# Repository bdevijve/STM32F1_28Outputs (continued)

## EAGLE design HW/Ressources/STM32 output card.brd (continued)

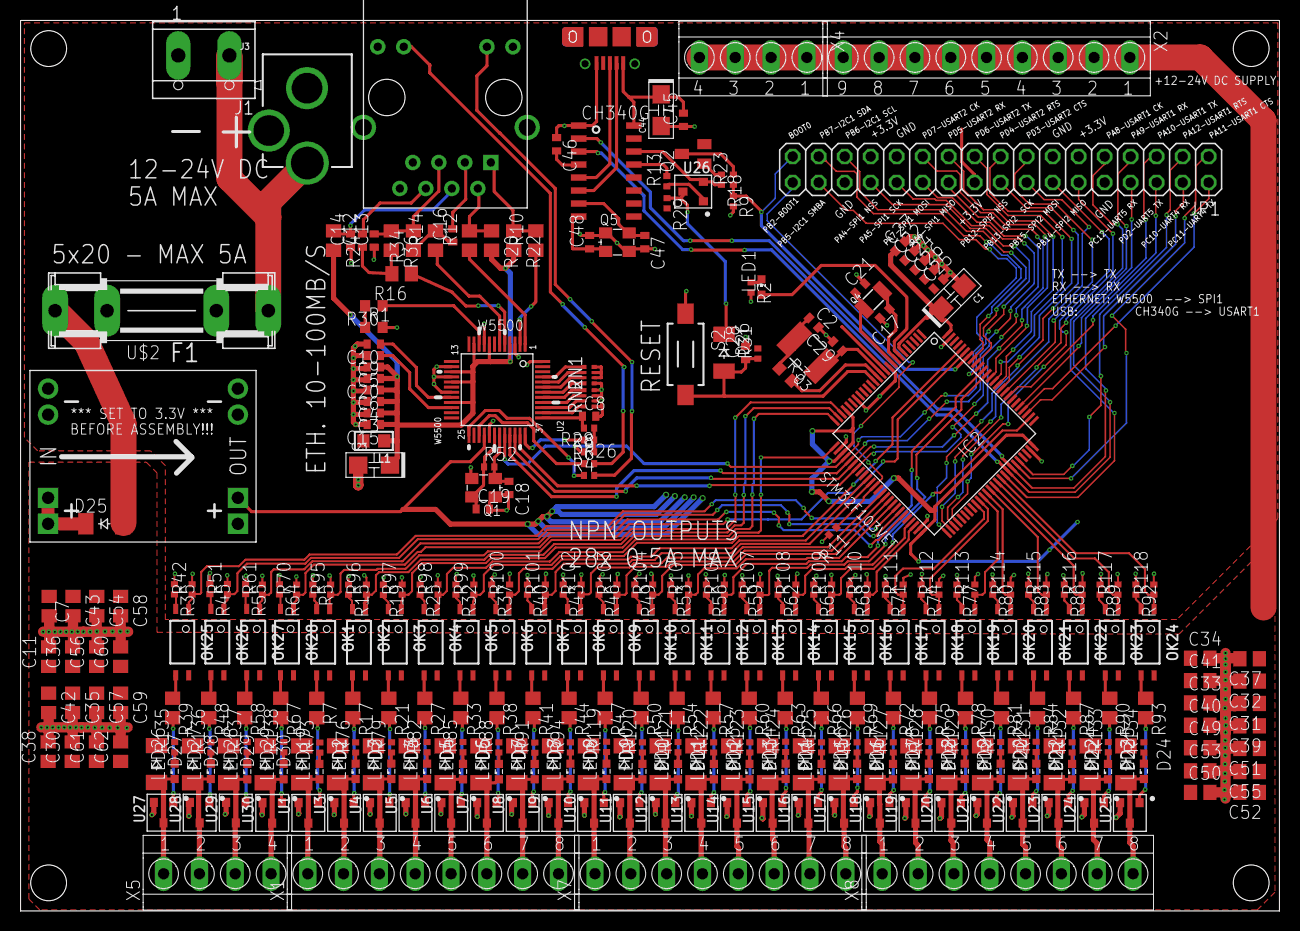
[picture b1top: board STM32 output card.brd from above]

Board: 2 copper layers, 123.0 x 87.0 mm, 341 parts (0 on the bottom side), 253 nets.

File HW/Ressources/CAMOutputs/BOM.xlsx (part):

COMMENT | DESIGNATOR | FOOTPRINT | Device | Description | PART NUMBER
 | LED1 | CHIP-LED0603 |  | LED | C2286
 | LED2 | SML0603 |  | LED | C2286
 | LED3 | SML0603 |  | LED | C2286
 | LED4 | SML0603 |  | LED | C2286
 | LED5 | SML0603 |  | LED | C2286
 | LED6 | SML0603 |  | LED | C2286
 | LED7 | SML0603 |  | LED | C2286
 | LED8 | SML0603 |  | LED | C2286
 | LED9 | SML0603 |  | LED | C2286
 | LED10 | SML0603 |  | LED | C2286
 | LED11 | SML0603 |  | LED | C2286
 | LED12 | SML0603 |  | LED | C2286
 | LED13 | SML0603 |  | LED | C2286
 | LED14 | SML0603 |  | LED | C2286
 | LED15 | SML0603 |  | LED | C2286
 | LED16 | SML0603 |  | LED | C2286
 | LED17 | SML0603 |  | LED | C2286
 | LED18 | SML0603 |  | LED | C2286
 | LED19 | SML0603 |  | LED | C2286
 | LED20 | SML0603 |  | LED | C2286
 | LED21 | SML0603 |  | LED | C2286
 | LED22 | SML0603 |  | LED | C2286
 | LED23 | SML0603 |  | LED | C2286
 | LED24 | SML0603 |  | LED | C2286
 | LED25 | SML0603 |  | LED | C2286
 | LED26 | SML0603 |  | LED | C2286
 | LED27 | SML0603 |  | LED | C2286
 | LED28 | SML0603 |  | LED | C2286
 | LED29 | SML0603 |  | LED | C2286
100K | R9 | R0402 |  | RESISTOR, European symbol | C25741
100K | R11 | R0402 |  | RESISTOR, European symbol | C25741
100K | R42 | R0402 |  | RESISTOR, European symbol | C25741
100K | R51 | R0402 |  | RESISTOR, European symbol | C25741
100K | R61 | R0402 |  | RESISTOR, European symbol | C25741
100K | R70 | R0402 |  | RESISTOR, European symbol | C25741
100K | R95 | R0402 |  | RESISTOR, European symbol | C25741
100K | R96 | R0402 |  | RESISTOR, European symbol | C25741
100K | R97 | R0402 |  | RESISTOR, European symbol | C25741
100K | R98 | R0402 |  | RESISTOR, European symbol | C25741
100K | R99 | R0402 |  | RESISTOR, European symbol | C25741
100K | R100 | R0402 |  | RESISTOR, European symbol | C25741
100K | R101 | R0402 |  | RESISTOR, European symbol | C25741
100K | R102 | R0402 |  | RESISTOR, European symbol | C25741
100K | R103 | R0402 |  | RESISTOR, European symbol | C25741
100K | R104 | R0402 |  | RESISTOR, European symbol | C25741
100K | R105 | R0402 |  | RESISTOR, European symbol | C25741
100K | R106 | R0402 |  | RESISTOR, European symbol | C25741
100K | R107 | R0402 |  | RESISTOR, European symbol | C25741
100K | R108 | R0402 |  | RESISTOR, European symbol | C25741
100K | R109 | R0402 |  | RESISTOR, European symbol | C25741
100K | R110 | R0402 |  | RESISTOR, European symbol | C25741
100K | R111 | R0402 |  | RESISTOR, European symbol | C25741
100K | R112 | R0402 |  | RESISTOR, European symbol | C25741
100K | R113 | R0402 |  | RESISTOR, European symbol | C25741
100K | R114 | R0402 |  | RESISTOR, European symbol | C25741
100K | R115 | R0402 |  | RESISTOR, European symbol | C25741
100K | R116 | R0402 |  | RESISTOR, European symbol | C25741
100K | R117 | R0402 |  | RESISTOR, European symbol | C25741
100K | R118 | R0402 |  | RESISTOR, European symbol | C25741
100nF | C3 | C0402 |  | CAPACITOR, European symbol | C1525
100nF | C4 | C0402 |  | CAPACITOR, European symbol | C1525
100nF | C5 | C0402 |  | CAPACITOR, European symbol | C1525
100nF | C6 | C0402 |  | CAPACITOR, European symbol | C1525
100nF | C8 | C0402 |  | CAPACITOR, European symbol | C1525
100nF | C15 | C0402 |  | CAPACITOR, European symbol | C1525
100nF | C20 | C0402 |  | CAPACITOR, European symbol | C1525
100nF | C22 | C0402 |  | CAPACITOR, European symbol | C1525
100nF | C24 | C0402 |  | CAPACITOR, European symbol | C1525
100nF | C25 | C0402 |  | CAPACITOR, European symbol | C1525
100nF | C26 | C0402 |  | CAPACITOR, European symbol | C1525
100nF | C27 | C0402 |  | CAPACITOR, European symbol | C1525
100pF | C45 | C0402 |  | CAPACITOR, European symbol | C1546
100pF | C46 | C0402 |  | CAPACITOR, European symbol | C1546
10K | R4 | R0402 |  | RESISTOR, European symbol | C25744
10K | R6 | R0402 |  | RESISTOR, European symbol | C25744
10K | R8 | R0402 |  | RESISTOR, European symbol | C25744
10K | R29 | R0402 |  | RESISTOR, European symbol | C25744
10K | R31 | R0402 |  | RESISTOR, European symbol | C25744
10K | RN1 | 4X0402ARV341 |  | Array Chip Resistor | C25725
10K | RN2 | 4X0402ARV341 |  | Array Chip Resistor | C25725
10nF | C9 | C0402 |  | CAPACITOR, European symbol | C15195
10nF | C13 | C0402 |  | CAPACITOR, European symbol | C15195
10pF | C17 | C0402 |  | CAPACITOR, European symbol | C32949
10pF | C21 | C0402 |  | CAPACITOR, European symbol | C32949
10uF/16V | C1 | C-3216(TANTAL) |  |  | C7171
10uF/16V | C23 | C-3216(TANTAL) |  |  | C7171
10uF/16V | C44 | C-3216(TANTAL) |  |  | C7171
12MHz | Q5 | 3.2X2.5_KX-7 |  | Quartz Crystals (MHz) SMD: | C9002
18pF | C18 | C0402 |  | CAPACITOR, European symbol | C1549
18pF | C19 | C0402 |  | CAPACITOR, European symbol | C1549
1ÂµF | C28 | C0402 |  | CAPACITOR, European symbol | C52923
1K | R13 | R0402 |  | RESISTOR, European symbol | C11702
1K | R18 | R0402 |  | RESISTOR, European symbol | C11702
1K | R23 | R0402 |  | RESISTOR, European symbol | C11702
1M | R52 | R0402 |  | RESISTOR, European symbol | C26083
20pF | C2 | C0402 |  | CAPACITOR, European symbol | C1554
20pF | C29 | C0402 |  | CAPACITOR, European symbol | C1554
22nF | C14 | C0402 |  | CAPACITOR, European symbol | C1532
22pF | C47 | C0402 |  | CAPACITOR, European symbol | C1555
22pF | C48 | C0402 |  | CAPACITOR, European symbol | C1555
25MHz | Q1 | 3.2X2.5_KX-7 |  | Quartz Crystals (MHz) SMD: | C9006
32.768KHz | Q4 | 3.2X1.5 |  | Tuning Fork Crystals (kHz) SMD: | C32346
330R | R26 | R0402 |  | RESISTOR, European symbol | C25104
330R | R28 | R0402 |  | RESISTOR, European symbol | C25104
33R | R10 | R0805 |  | RESISTOR, European symbol | C17634
33R | R12 | R0805 |  | RESISTOR, European symbol | C17634
33R | R14 | R0805 |  | RESISTOR, European symbol | C17634
33R | R16 | R0805 |  | RESISTOR, European symbol | C17634
390R | R3 | R0603 |  | RESISTOR, European symbol | C23151
3K | R7 | R0805 |  | RESISTOR, European symbol | C17661
3K | R17 | R0805 |  | RESISTOR, European symbol | C17661
3K | R21 | R0805 |  | RESISTOR, European symbol | C17661
3K | R27 | R0805 |  | RESISTOR, European symbol | C17661
3K | R33 | R0805 |  | RESISTOR, European symbol | C17661
3K | R38 | R0805 |  | RESISTOR, European symbol | C17661
3K | R39 | R0805 |  | RESISTOR, European symbol | C17661
3K | R41 | R0805 |  | RESISTOR, European symbol | C17661
3K | R44 | R0805 |  | RESISTOR, European symbol | C17661
3K | R47 | R0805 |  | RESISTOR, European symbol | C17661
3K | R48 | R0805 |  | RESISTOR, European symbol | C17661
3K | R50 | R0805 |  | RESISTOR, European symbol | C17661
3K | R54 | R0805 |  | RESISTOR, European symbol | C17661
3K | R57 | R0805 |  | RESISTOR, European symbol | C17661
3K | R58 | R0805 |  | RESISTOR, European symbol | C17661
3K | R60 | R0805 |  | RESISTOR, European symbol | C17661
3K | R63 | R0805 |  | RESISTOR, European symbol | C17661
3K | R66 | R0805 |  | RESISTOR, European symbol | C17661
3K | R67 | R0805 |  | RESISTOR, European symbol | C17661
3K | R69 | R0805 |  | RESISTOR, European symbol | C17661
3K | R72 | R0805 |  | RESISTOR, European symbol | C17661
3K | R75 | R0805 |  | RESISTOR, European symbol | C17661
3K | R78 | R0805 |  | RESISTOR, European symbol | C17661
3K | R81 | R0805 |  | RESISTOR, European symbol | C17661
3K | R84 | R0805 |  | RESISTOR, European symbol | C17661
3K | R87 | R0805 |  | RESISTOR, European symbol | C17661
3K | R90 | R0805 |  | RESISTOR, European symbol | C17661
3K | R93 | R0805 |  | RESISTOR, European symbol | C17661
4.7ÂµF | C10 | C0402 |  | CAPACITOR, European symbol | C23733
470nF - 50V | C7 | C0805 |  | CAPACITOR, European symbol | C13967
470nF - 50V | C11 | C0805 |  | CAPACITOR, European symbol | C13967
470nF - 50V | C30 | C0805 |  | CAPACITOR, European symbol | C13967
470nF - 50V | C31 | C0805 |  | CAPACITOR, European symbol | C13967
470nF - 50V | C32 | C0805 |  | CAPACITOR, European symbol | C13967
470nF - 50V | C33 | C0805 |  | CAPACITOR, European symbol | C13967
470nF - 50V | C34 | C0805 |  | CAPACITOR, European symbol | C13967
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
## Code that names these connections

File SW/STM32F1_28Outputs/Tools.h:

#define MQTT_STRING_LEN 128
char dynamicTopic [MQTT_STRING_LEN];
#define STRING_LEN 30

struct STRUCT_Settings {
  char deviceName                 [STRING_LEN];
  IPAddress mqttServerIP          ;
  char mqttPrefix                 [STRING_LEN];
  char subTopicStatus             [STRING_LEN];
  char subTopicSet                [STRING_LEN];
  char subTopicUptime             [STRING_LEN];
  char subTopicLoopIterationCount [STRING_LEN];
  char subTopicfreeMemory         [STRING_LEN];
};

struct STRUCT_Settings settings = (STRUCT_Settings) {
  "carte1",
  IPAddress(192,168,1,22),
  "carterelais",
  "status", 
  "set",
  "uptime",
  "loopiterationcount",
  "freeMemory"
};

uint16_t GPIOINIT_TABLE[] = {
  PA0, PA1, PA2, PA3, PA4, PA5, PA6, PA7, PA8, PA9, PA10, PA11, PA12, PA13, PA14, PA15,
  PB0, PB1, PB2, PB3, PB4, PB5, PB6, PB7, PB8, PB9, PB10, PB11, PB12, PB13, PB14, PB15,
  PC0, PC1, PC2, PC3, PC4, PC5, PC6, PC7, PC8, PC9, PC10, PC11, PC12, PC13, PC14, PC15,
  PD0, PD1, PD2, PD3, PD4, PD5, PD6, PD7, PD8, PD9, PD10, PD11, PD12, PD13, PD14, PD15,
  PE0, PE1, PE2, PE3, PE4, PE5, PE6, PE7, PE8, PE9, PE10, PE11, PE12, PE13, PE14, PE15,
  0xffff
};

#define OUTPUT_COUNT 28       // Nb de sortie externe réel, sachant que la LED interne d'état sera comptabilisé en +

uint8_t GPIO_OUTPUT[] = {
  PC13, PE12, PE13, PE14, PB8, PA0, PA1, PA2, PA3, PB9, PB0, PB1, PE8, PE9, PE10, PE11, PB4, PB3, PA15, PB10, PB11, PD12, PD13, PD14, PD15, PC6, PC7, PC8, PC9
};

uint8_t isON [] = {0,0,0,0,0,0,0,0,0,0,0,0,0,0,0,0,0,0,0,0,0,0,0,0,0,0,0,0,0} ;


void readStoredVariables() {
  char buf ;
  char readString [STRING_LEN];

  //Lecture du tag
  for (uint8_t i=0 ; i< STRING_LEN; i++){
    EEPROM.get(i, buf);
    readString[i] = buf;    
  }
  
  if  (strcmp(readString, "OK") != 0){
    #ifdef SERIALDEBUG1
      Serial.println("Mise à zéro EEPROM");
    #endif

    EEPROM.put(STRING_LEN, settings);
    EEPROM.put(0, "OK");
    } else {
    #ifdef SERIALDEBUG1
      Serial.println("EEPROM déjà initialisée");
      EEPROM.get(STRING_LEN, settings);
    #endif
    }
}

void doON(uint8_t channel){

  char topicOut [MQTT_STRING_LEN];
  char convert [5];

  #ifndef KEEP_BUG
    if (channel <= OUTPUT_COUNT) 
  #endif
  {
    digitalWrite(GPIO_OUTPUT[channel], 1);
    isON[channel] = 1 ;
    #ifdef SERIALDEBUG9
      { long now = millis(); Serial.print(now); }  Serial.print (" - Got it! ON - channel "); Serial.println (channel);
    #endif
    strcpy (topicOut,dynamicTopic);
    sprintf (convert, "%i", channel);
    strcat (topicOut, convert);
    strcat (topicOut, "/");
    strcat (topicOut, settings.subTopicStatus);
    mqttClient.publish(topicOut, "1", true);
  }
}

void doOFF(uint8_t channel){
  char topicOut [MQTT_STRING_LEN];
  char convert [5];
  
  #ifndef KEEP_BUG
    if (channel <= OUTPUT_COUNT) 
  #endif
  {
    digitalWrite(GPIO_OUTPUT[channel], 0);
    isON[channel] = 0 ;
    #ifdef SERIALDEBUG9
      { long now = millis(); Serial.print(now); }  Serial.print (" - Got it! OFF - channel "); Serial.println (channel);
    #endif
    strcpy (topicOut,dynamicTopic);
    sprintf (convert, "%i", channel);
    strcat (topicOut, convert);
    strcat (topicOut, "/");
    strcat (topicOut, settings.subTopicStatus);
    mqttClient.publish(topicOut, "0", true);
  }
}

void doTOGGLE(uint8_t channel){
  #ifndef KEEP_BUG
    if (channel <= OUTPUT_COUNT) 
  #endif
  {
   if (isON[channel]) doOFF(channel); else doON(channel);
  }
}

#ifdef __arm__
// should use uinstd.h to define sbrk but Due causes a conflict
extern "C" char* sbrk(int incr);
#else  // __ARM__
extern char *__brkval;
#endif  // __arm__
 
int freeMemory() {
  char top;
#ifdef __arm__
  return &top - reinterpret_cast<char*>(sbrk(0));
#elif defined(CORE_TEENSY) || (ARDUINO > 103 && ARDUINO != 151)
  return &top - __brkval;
#else  // __arm__
  return __brkval ? &top - __brkval : &top - __malloc_heap_start;
#endif  // __arm__
}

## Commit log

2021-01-08 SYNC
